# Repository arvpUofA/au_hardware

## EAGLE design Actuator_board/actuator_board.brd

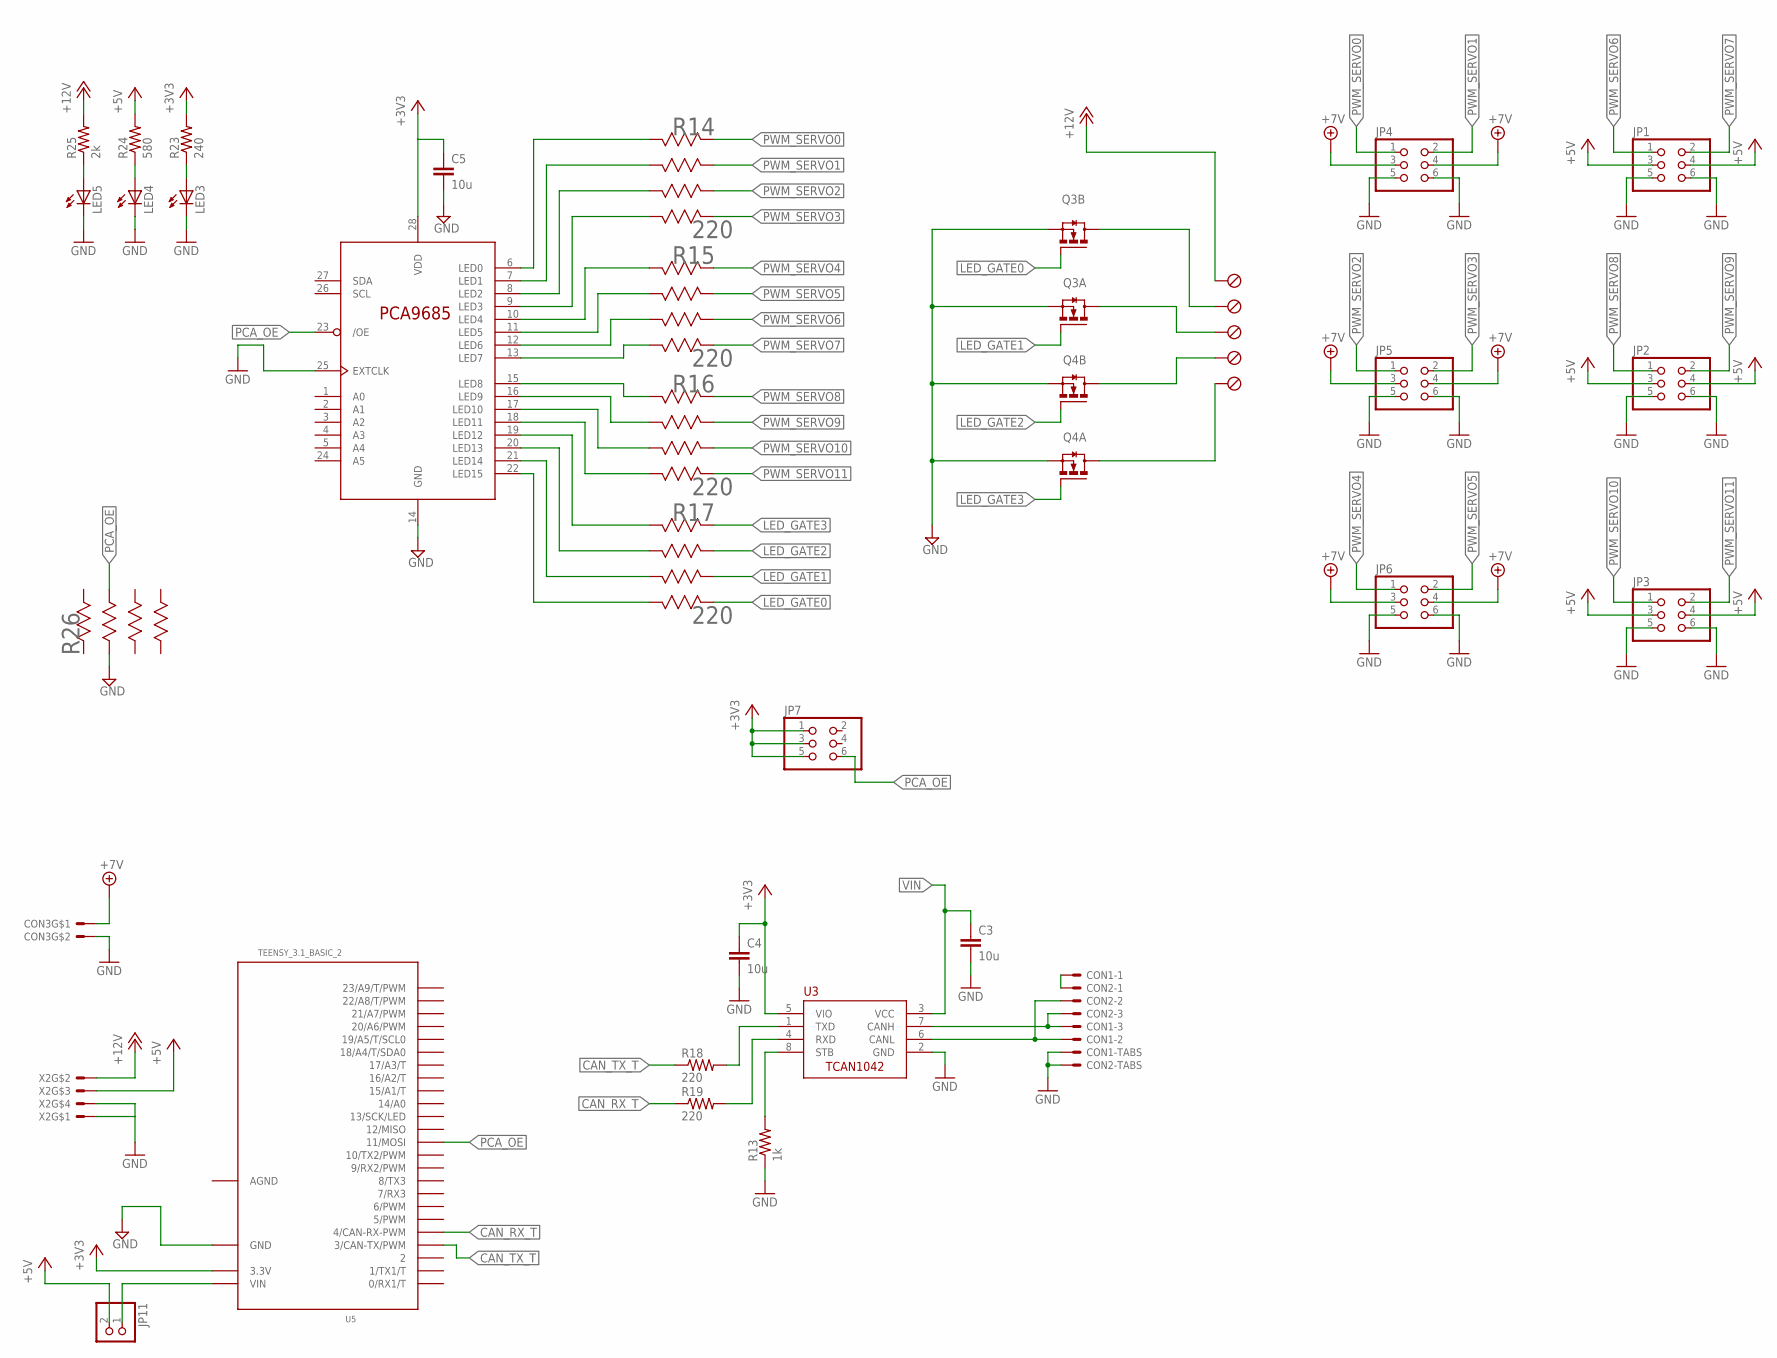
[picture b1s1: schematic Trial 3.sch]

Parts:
C3, C4, C5: 10u; C0805
CON1, CON2: SM03B-GHS-TB
CON3: MOLEX_5566-2; 5566-2
JP1, JP2, JP3, JP4, JP5, JP6, JP7: PINHD-2X3; 2X03
JP11: PINHD-1X2; 1X02
LED3, LED4, LED5: LEDCHIPLED_1206; CHIPLED_1206
Q3, Q4: IRL6372TRPBF; SO-8
R13: 1k; R0805
R14, R15, R16, R17: 220; EXBV8V-M
R18, R19: 220; R0805
R23: 240; R1206
R24: 580; R1206
R25: 2k; R1206
R26: 10k; EXBV8V-M
U3: TCAN1042HVDR; SO-8
U4: PCA9685PW; TSSOP28
U5: TEENSY_3.1_BASIC_2
U$1: SCREWLESS_TERMINAL_HEADERSCREWLESS_TERMINAL_HEADER; 1989777_TERMINALHEADER
X2: MOLEX_5566-4; 5566-4

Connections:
+3V3: C4.1, C5.1, JP7.1, JP7.3, JP7.5, R23.2, U3.5 (VIO), U4.28 (VDD), U5.3.3V
+5V: JP1.3, JP1.4, JP2.3, JP2.4, JP3.3, JP3.4, JP11.2, R24.2, X2.3
+7V: CON3.1, JP4.3, JP4.4, JP5.3, JP5.4, JP6.3, JP6.4
+12V: R25.2, U$1.P$5 (12+), X2.2; also elsewhere on the board
AGND: U5.AGND
CANH: CON1.P$3, CON2.P$3, U3.7 (CANH)
CANL: CON1.P$2, CON2.P$2, U3.6 (CANL)
CANSH: CON1.P$1, CON2.P$1
CAN_RX: R19.2, U3.4 (RXD)
CAN_RX_T: R19.1, U5.4 (4/CAN-RX-PWM)
CAN_TX1: R18.2, U3.1 (TXD)
CAN_TX_T: R18.1, U5.3 (3/CAN-TX/PWM)
GND: C3.2, C4.2, C5.2, CON1.P$4, CON1.P$5, CON2.P$4, CON2.P$5, CON3.2, JP1.5, JP1.6, JP2.5, JP2.6, JP3.5, JP3.6, JP4.5, JP4.6, JP5.5, JP5.6, JP6.5, JP6.6, LED3.C, LED4.C, LED5.C, Q3.1 (S), Q3.3 (S), Q4.1 (S), Q4.3 (S), R13.1, R26.2 (23), U3.2 (GND), U4.14 (GND), U4.25 (EXTCLK), U5.GND, X2.1, X2.4
LED_DRAIN0: Q3.7 (D), Q3.8 (D), U$1.P$4 (LED0); also elsewhere on the board
LED_DRAIN1: Q3.5 (D), Q3.6 (D), U$1.P$3 (LED1); also elsewhere on the board
LED_DRAIN2: Q4.7 (D), Q4.8 (D), U$1.P$2 (LED2); also elsewhere on the board
LED_DRAIN3: Q4.5 (D), Q4.6 (D), U$1.P$1 (LED3); also elsewhere on the board
LED_GATE0: Q3.2 (G), R17.4 (47)
LED_GATE1: Q3.4 (G), R17.3 (35)
LED_GATE2: Q4.2 (G), R17.2 (23)
LED_GATE3: Q4.4 (G), R17.1 (11)
unnamed: LED3.A, R23.1
unnamed: LED4.A, R24.1
unnamed: LED5.A, R25.1
PCA_OE: JP7.6, R26.7 (74), U4.23 (/OE), U5.11 (11/MOSI)
PWM_CH0: R14.8 (82), U4.6 (LED0)
PWM_CH1: R14.7 (74), U4.7 (LED1)
PWM_CH2: R14.6 (66), U4.8 (LED2)
PWM_CH3: R14.5 (58), U4.9 (LED3)
PWM_CH4: R15.8 (82), U4.10 (LED4)
PWM_CH5: R15.7 (74), U4.11 (LED5)
PWM_CH6: R15.6 (66), U4.12 (LED6)
PWM_CH7: R15.5 (58), U4.13 (LED7)
PWM_CH8: R16.8 (82), U4.15 (LED8)
PWM_CH9: R16.7 (74), U4.16 (LED9)
PWM_CH10: R16.6 (66), U4.17 (LED10)
PWM_CH11: R16.5 (58), U4.18 (LED11)
PWM_CH12: R17.8 (82), U4.19 (LED12)
PWM_CH13: R17.7 (74), U4.20 (LED13)
PWM_CH14: R17.6 (66), U4.21 (LED14)
PWM_CH15: R17.5 (58), U4.22 (LED15)
PWM_SERVO0: JP4.1, R14.1 (11)
PWM_SERVO1: JP4.2, R14.2 (23)
PWM_SERVO2: JP5.1, R14.3 (35)
PWM_SERVO3: JP5.2, R14.4 (47)
PWM_SERVO4: JP6.1, R15.1 (11)
PWM_SERVO5: JP6.2, R15.2 (23)
PWM_SERVO6: JP1.1, R15.3 (35)
PWM_SERVO7: JP1.2, R15.4 (47)
PWM_SERVO8: JP2.1, R16.1 (11)
PWM_SERVO9: JP2.2, R16.2 (23)
PWM_SERVO10: JP3.1, R16.3 (35)
PWM_SERVO11: JP3.2, R16.4 (47)
STB: R13.2, U3.8 (STB)
VIN: C3.1, JP11.1, U3.3 (VCC), U5.VIN

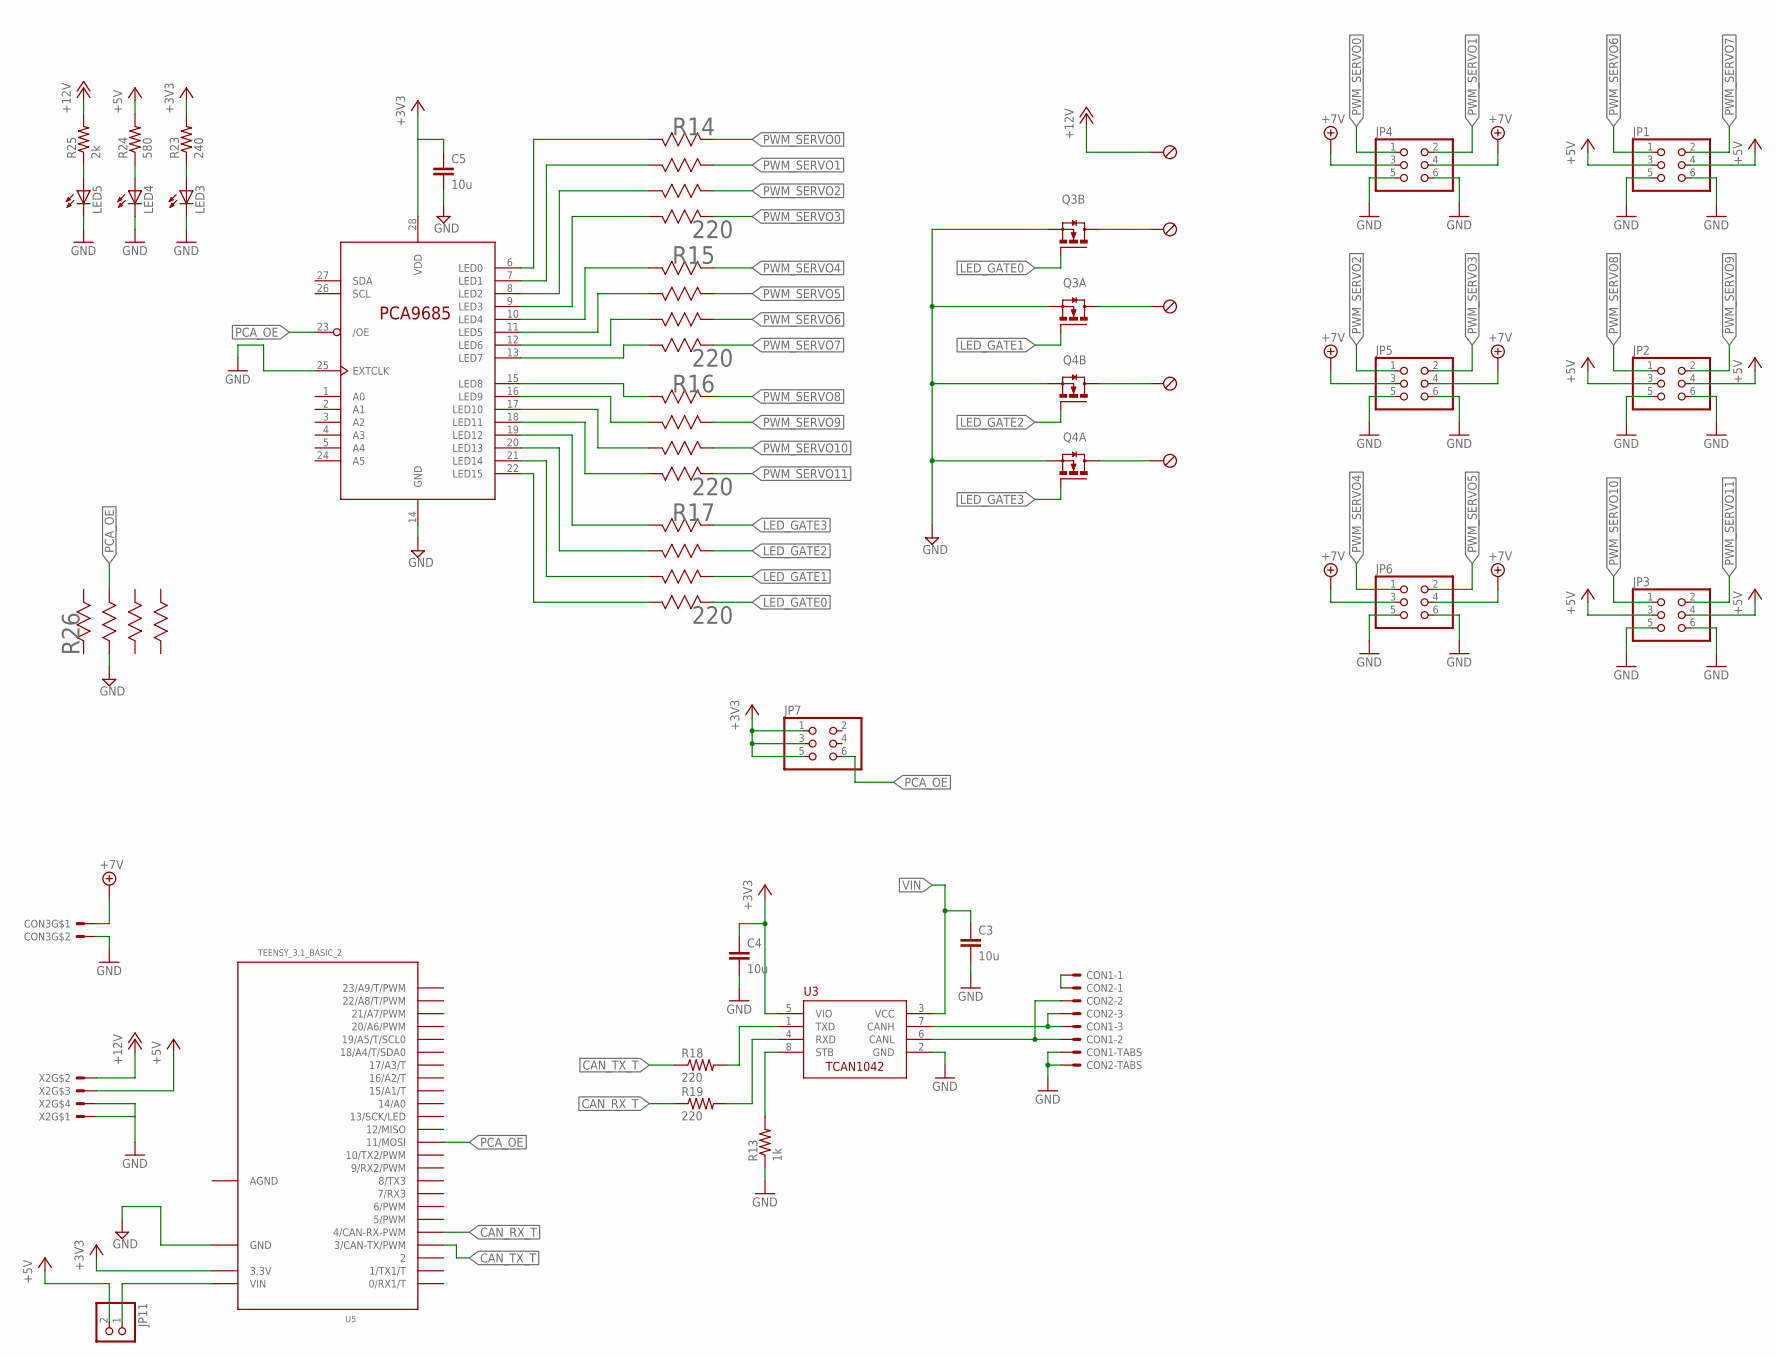
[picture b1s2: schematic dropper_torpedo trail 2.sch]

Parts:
C3, C4, C5: 10u; C0805
CON1, CON2: SM03B-GHS-TB
CON3: MOLEX_5566-2; 5566-2
JP1, JP2, JP3, JP4, JP5, JP6, JP7: PINHD-2X3; 2X03
JP11: PINHD-1X2; 1X02
LED3, LED4, LED5: LEDCHIPLED_1206; CHIPLED_1206
Q3, Q4: IRL6372TRPBF; SO-8
R13: 1k; R0805
R14, R15, R16, R17: 220; EXBV8V-M
R18, R19: 220; R0805
R23: 240; R1206
R24: 580; R1206
R25: 2k; R1206
R26: 10k; EXBV8V-M
U3: TCAN1042HVDR; SO-8
U4: PCA9685PW; TSSOP28
U5: TEENSY_3.1_BASIC_2
X1: OSTVN05A150
X2: MOLEX_5566-4; 5566-4

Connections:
+3V3: C4.1, C5.1, JP7.1, JP7.3, JP7.5, R23.2, U3.5 (VIO), U4.28 (VDD), U5.3.3V
+5V: JP1.3, JP1.4, JP2.3, JP2.4, JP3.3, JP3.4, JP11.2, R24.2, X2.3
+7V: CON3.1, JP4.3, JP4.4, JP5.3, JP5.4, JP6.3, JP6.4
+12V: R25.2, X1.P$5, X2.2; also elsewhere on the board
AGND: U5.AGND
CANH: CON1.P$3, CON2.P$3, U3.7 (CANH)
CANL: CON1.P$2, CON2.P$2, U3.6 (CANL)
CANSH: CON1.P$1, CON2.P$1
CAN_RX: R19.2, U3.4 (RXD)
CAN_RX_T: R19.1, U5.4 (4/CAN-RX-PWM)
CAN_TX1: R18.2, U3.1 (TXD)
CAN_TX_T: R18.1, U5.3 (3/CAN-TX/PWM)
GND: C3.2, C4.2, C5.2, CON1.P$4, CON1.P$5, CON2.P$4, CON2.P$5, CON3.2, JP1.5, JP1.6, JP2.5, JP2.6, JP3.5, JP3.6, JP4.5, JP4.6, JP5.5, JP5.6, JP6.5, JP6.6, LED3.C, LED4.C, LED5.C, Q3.1 (S), Q3.3 (S), Q4.1 (S), Q4.3 (S), R13.1, R26.2 (23), U3.2 (GND), U4.14 (GND), U4.25 (EXTCLK), U5.GND, X2.1, X2.4
LED_DRAIN0: Q3.7 (D), Q3.8 (D), X1.P$4; also elsewhere on the board
LED_DRAIN1: Q3.5 (D), Q3.6 (D), X1.P$3; also elsewhere on the board
LED_DRAIN2: Q4.7 (D), Q4.8 (D), X1.P$2; also elsewhere on the board
LED_DRAIN3: Q4.5 (D), Q4.6 (D), X1.P$1; also elsewhere on the board
LED_GATE0: Q3.2 (G), R17.4 (47)
LED_GATE1: Q3.4 (G), R17.3 (35)
LED_GATE2: Q4.2 (G), R17.2 (23)
LED_GATE3: Q4.4 (G), R17.1 (11)
unnamed: LED3.A, R23.1
unnamed: LED4.A, R24.1
unnamed: LED5.A, R25.1
PCA_OE: JP7.6, R26.7 (74), U4.23 (/OE), U5.11 (11/MOSI)
PWM_CH0: R14.8 (82), U4.6 (LED0)
PWM_CH1: R14.7 (74), U4.7 (LED1)
PWM_CH2: R14.6 (66), U4.8 (LED2)
PWM_CH3: R14.5 (58), U4.9 (LED3)
PWM_CH4: R15.8 (82), U4.10 (LED4)
PWM_CH5: R15.7 (74), U4.11 (LED5)
PWM_CH6: R15.6 (66), U4.12 (LED6)
PWM_CH7: R15.5 (58), U4.13 (LED7)
PWM_CH8: R16.8 (82), U4.15 (LED8)
PWM_CH9: R16.7 (74), U4.16 (LED9)
PWM_CH10: R16.6 (66), U4.17 (LED10)
PWM_CH11: R16.5 (58), U4.18 (LED11)
PWM_CH12: R17.8 (82), U4.19 (LED12)
PWM_CH13: R17.7 (74), U4.20 (LED13)
PWM_CH14: R17.6 (66), U4.21 (LED14)
PWM_CH15: R17.5 (58), U4.22 (LED15)
PWM_SERVO0: JP4.1, R14.1 (11)
PWM_SERVO1: JP4.2, R14.2 (23)
PWM_SERVO2: JP5.1, R14.3 (35)
PWM_SERVO3: JP5.2, R14.4 (47)
PWM_SERVO4: JP6.1, R15.1 (11)
PWM_SERVO5: JP6.2, R15.2 (23)
PWM_SERVO6: JP1.1, R15.3 (35)
PWM_SERVO7: JP1.2, R15.4 (47)
PWM_SERVO8: JP2.1, R16.1 (11)
PWM_SERVO9: JP2.2, R16.2 (23)
PWM_SERVO10: JP3.1, R16.3 (35)
PWM_SERVO11: JP3.2, R16.4 (47)
STB: R13.2, U3.8 (STB)
VIN: C3.1, JP11.1, U3.3 (VCC), U5.VIN

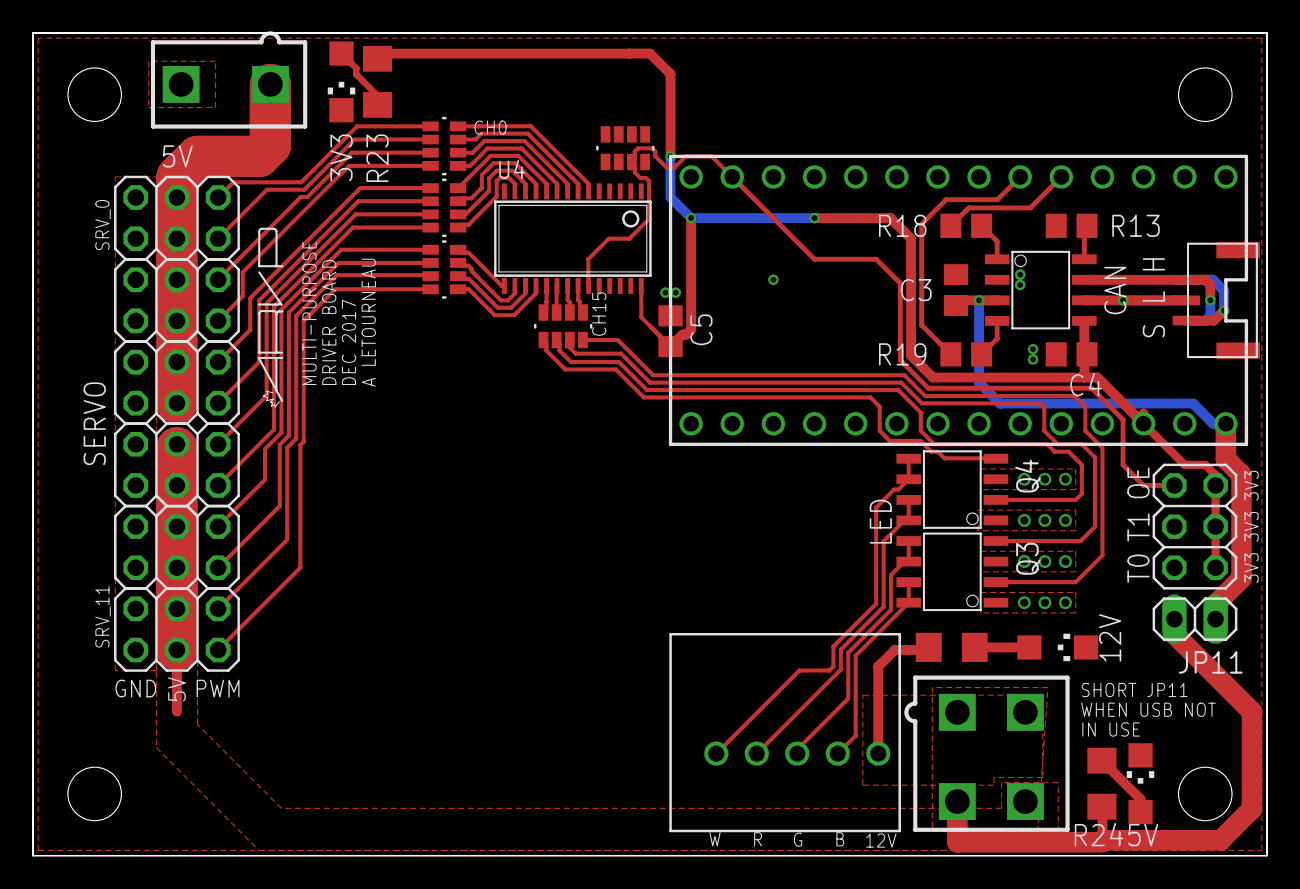
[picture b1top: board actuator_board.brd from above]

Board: 2 copper layers, 76.2 x 50.8 mm, 42 parts (1 on the bottom side), 54 nets.

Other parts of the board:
U$5: LOGO3
U$6: LETTER_L
U$7: DOCFIELD
U$8, U$9, U$10, U$11: STAND-OFF

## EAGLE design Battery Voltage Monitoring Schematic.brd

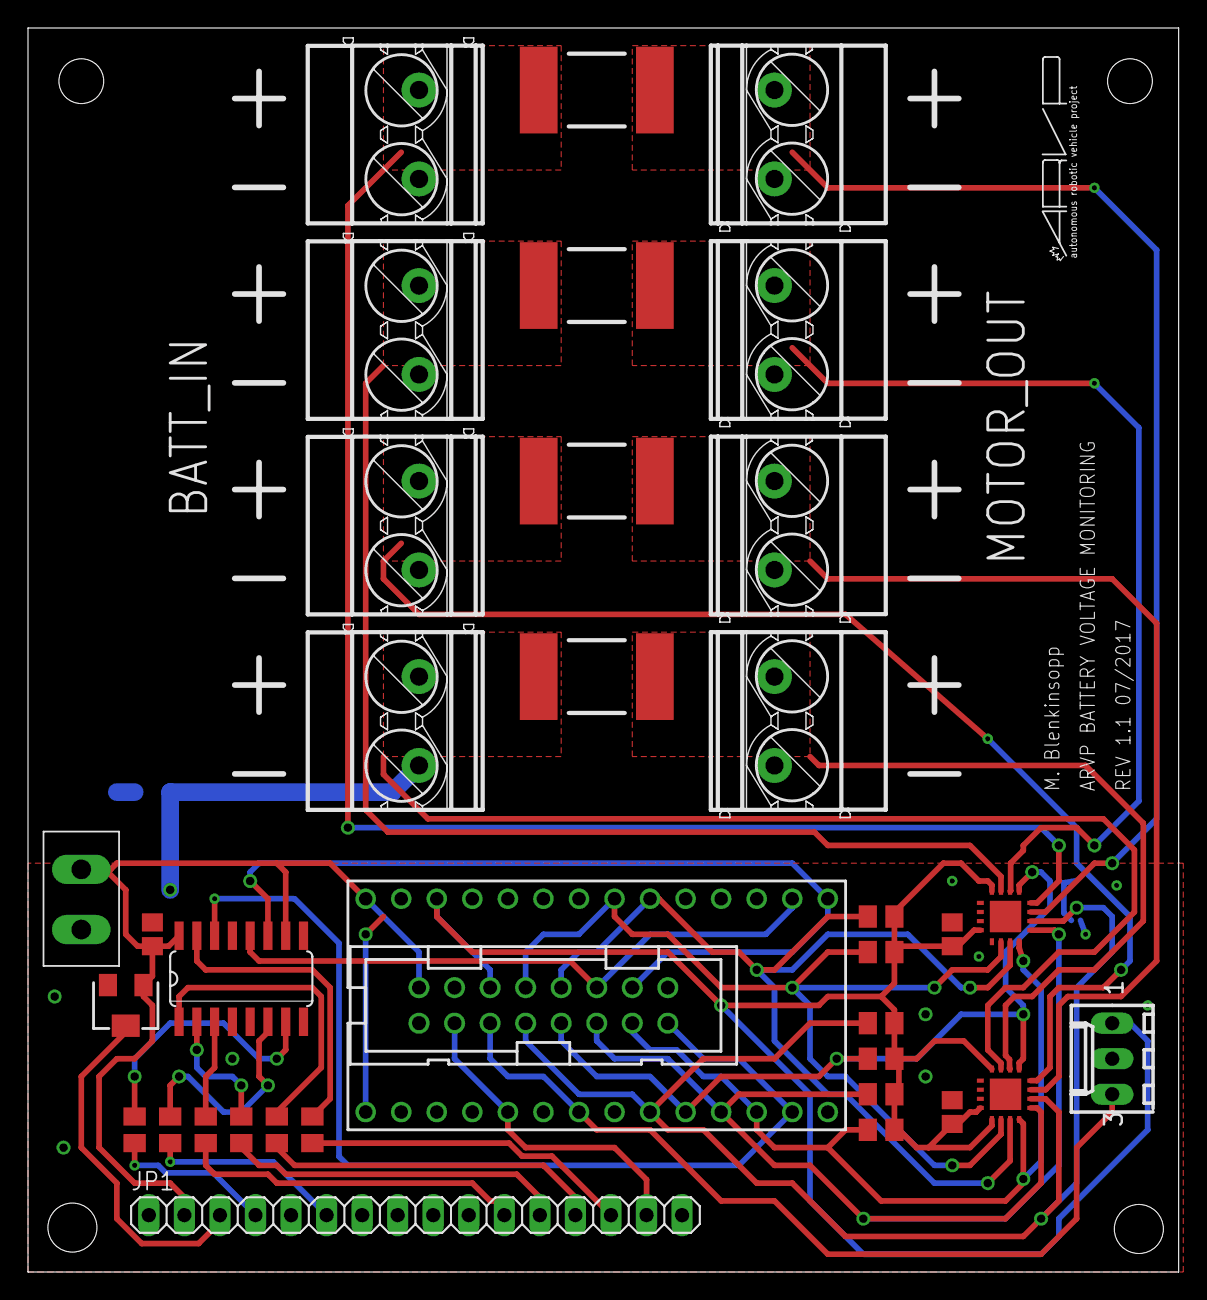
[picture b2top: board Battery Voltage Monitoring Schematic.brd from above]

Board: 2 copper layers, 82.2 x 88.9 mm, 37 parts (0 on the bottom side), 36 nets.

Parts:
C1, C2, C4: 0.1microF; C2012
IC1: 74HC595D; SO16
J1: 22-27-2031-03; 6410-03
JP1: 1X16
R1, R3, R4, R7: 0.001Ohm; 3920
R2, R5, R6, R8, R9, R10: 10kOhm; M2012
R11, R12, R13, R14, R15, R16: 560Ohm; M2012
R22: 10kOhm; SM-42/43W
U1, U2: INA3221.; HVQFN16_4X4
U$1, U$2, U$3, U$4, U$5, U$6, U$7, U$11: MKDS_5/2-6,352; MKDS_5/2-6,35
U$9: ARVP_MOLEX_FEMALE
U$10: ARVP_LOGO; ARVP
U$14: TEENSY_3.1-3.2_DIL; TEENSY_3.0-3.2&LC_DIL
X3: 2516-; PAK100/2500-16

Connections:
0-26V_BATTERY1: R4.P$2, U1.12, U$1.1
0-26V_BATTERY2: R1.P$2, U1.15, U$2.1
0-26V_BATTERY3: R3.P$2, U2.12, U$3.1
0-26V_BATTERY4: R7.P$2, U2.15, U$4.1
3.3V: C2.1, C4.1, J1.1, R2.1, R5.2, R6.2, R8.2, R9.2, R10.2, U1.4, U1.16, U2.4, U2.5, U2.16, U$14.3.3V, X3.6
+5V: C1.1, IC1.10, IC1.16, JP1.2, R22.1, U$9.P$1, U$14.VIN, X3.2
AGND: U$14.AGND, X3.4
BACKLIGHT: JP1.15, U$14.3, X3.3
CRITICAL_OUT: R8.1, U1.9, U2.9, U$14.9, X3.11
DATA: IC1.14, U$14.11, X3.15
ENABLE: JP1.6, R12.2
ENABLE1: IC1.6, R12.1
GND: C1.2, C2.2, C4.2, IC1.5, IC1.8, IC1.13, J1.2, JP1.1, JP1.5, JP1.16, R22.3, U1.3, U1.5, U2.3, U$1.2, U$2.2, U$3.2, U$4.2, U$5.1, U$6.1, U$7.1, U$9.P$2, U$11.1, U$14.GND, X3.1
HALL: J1.3, U$14.5, X3.5
LATCH: IC1.12, U$14.14/A0, X3.12
LCD(SCK): IC1.11, U$14.13, X3.14
LCD_DB4: JP1.11, R13.2
LCD_DB5: JP1.12, R14.2
LCD_DB6: JP1.13, R15.2
LCD_DB7: JP1.14, R16.1
LCD_DB41: IC1.3, R13.1
LCD_DB51: IC1.2, R14.1
LCD_DB61: IC1.1, R15.1
LCD_DB71: IC1.15, R16.2
MOTOR1: R4.P$1, U1.11, U$7.2
MOTOR2: R1.P$1, U1.14, U$6.2
MOTOR3: R3.P$1, U2.11, U$5.2
MOTOR4: R7.P$1, U2.14, U$11.2
unnamed: JP1.3, R22.2
PV_OUT: R2.2, U1.10, U2.10, U$14.7, X3.7
RS: JP1.4, R11.2
RS1: IC1.7, R11.1
SDA_OUT: R6.1, U1.7, U2.7, U$14.18/A4, X3.10
TC_OUT: R9.1, U1.13, U2.13, U$14.8, X3.9
TEENSY_SCK: R5.1, U1.6, U2.6, U$14.19/A5, X3.8
WARNING_OUT: R10.1, U1.8, U2.8, U$14.10, X3.13

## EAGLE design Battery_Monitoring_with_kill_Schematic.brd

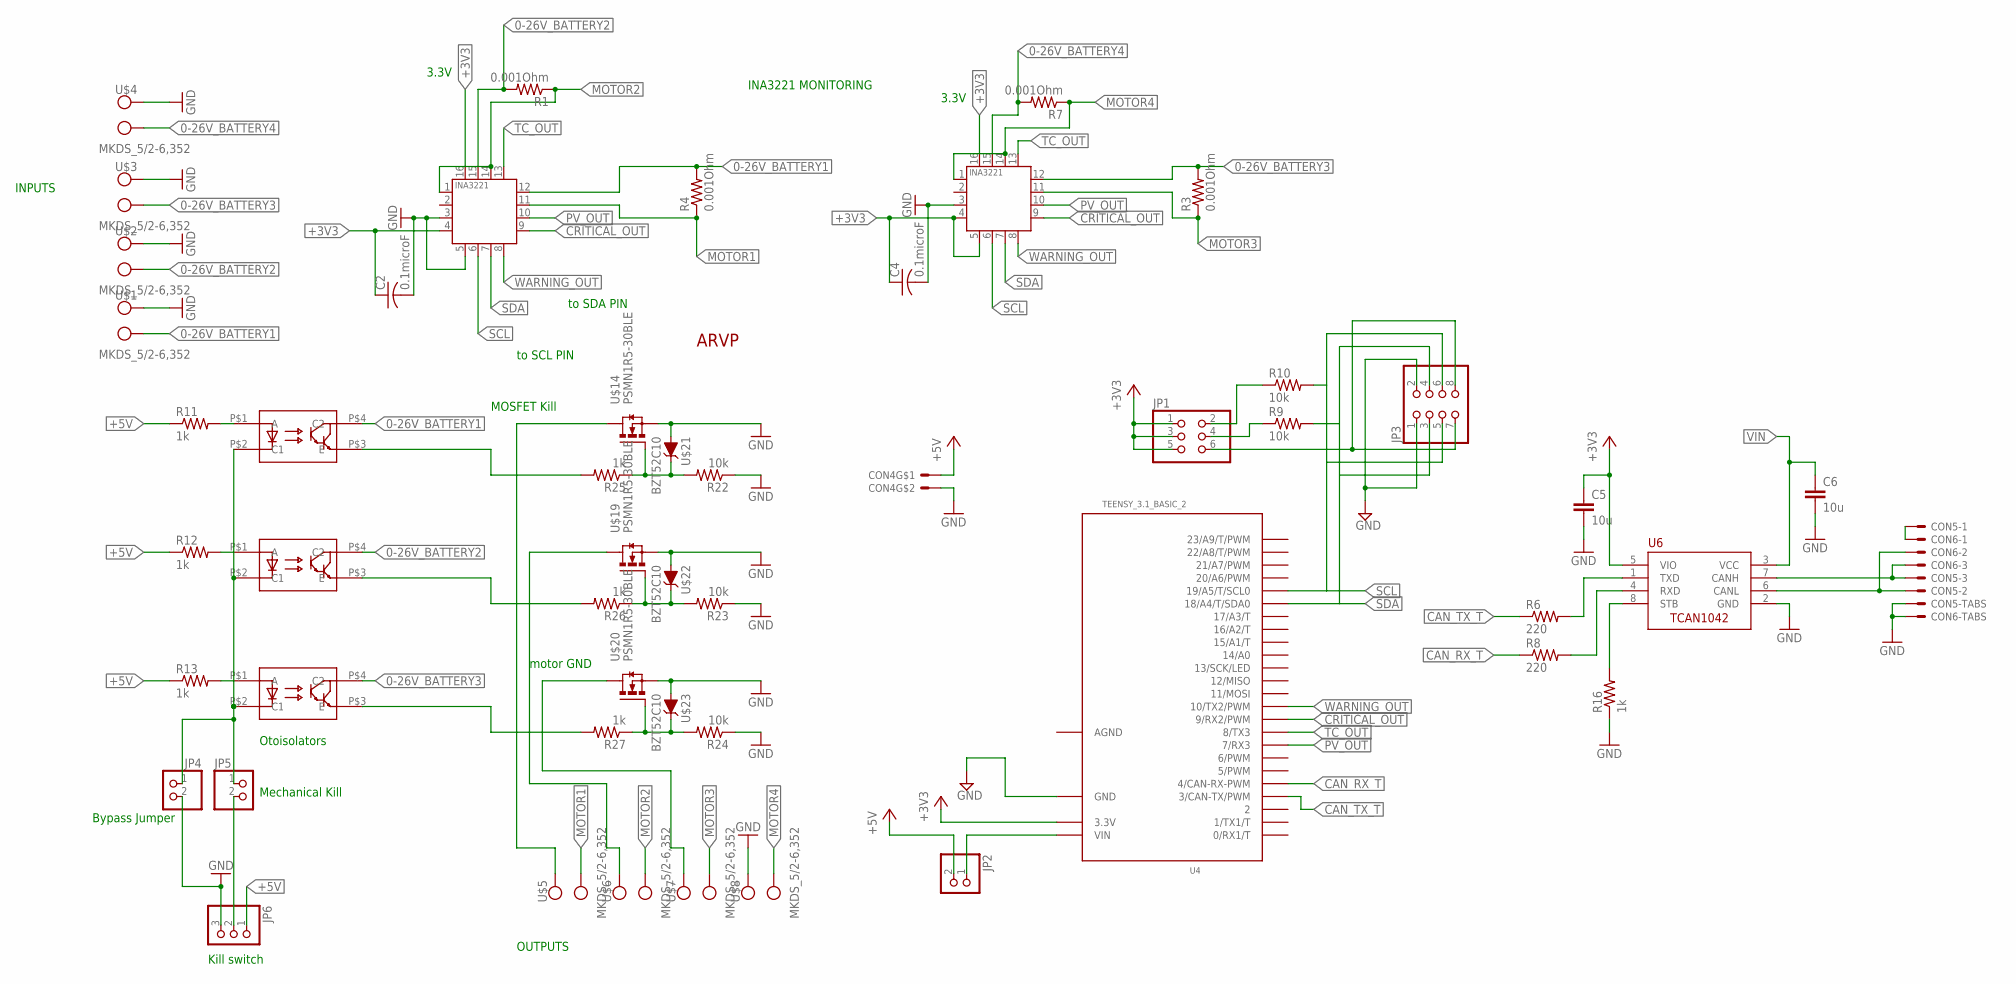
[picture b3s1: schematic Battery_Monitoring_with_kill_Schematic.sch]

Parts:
C2, C4: 0.1microF; C2012
C5, C6: 10u; C0805
CON4: MOLEX_5566-2; 5566-2
CON5, CON6: S3B-PH-SM4-TB
JP1: PINHD-2X3; 2X03
JP2, JP4, JP5: PINHD-1X2; 1X02
JP3: PINHD-2X4; 2X04
JP6: PINHD-1X3; 1X03
R1, R3, R4, R7: 0.001Ohm; 3920
R6, R8: 220; R0805
R9, R10: 10k; R1206
R11, R12, R13, R16: 1k; R0805
R22, R23, R24: 10k; M1206
R25, R26, R27: 1k; M1206
U1, U2: INA3221.; HVQFN16_4X4
U4: TEENSY_3.1_BASIC_2
U6: TCAN1042HVDR; SO-8
U$1, U$2, U$3, U$4, U$5, U$6, U$7, U$8: MKDS_5/2-6,352; MKDS_5/2-6,35
U$10: ARVP_LOGO; ARVP
U$11, U$12, U$13: TCLD1000CT; SOP-4L
U$14, U$19, U$20: PSMN1R5-30BLE; SOT404/D2PAK
U$21, U$22, U$23: BZT52C10; SOD-123

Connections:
0-26V_BATTERY1: R4.P$2 (2), U1.12 (IN+1), U$1.1 (KL), U$11.P$4 (C2)
0-26V_BATTERY2: R1.P$2 (2), U1.15 (IN+2), U$2.1 (KL), U$12.P$4 (C2)
0-26V_BATTERY3: R3.P$2 (2), U2.12 (IN+1), U$3.1 (KL), U$13.P$4 (C2)
0-26V_BATTERY4: R7.P$2 (2), U2.15 (IN+2), U$4.1 (KL)
+3V3: C2.1, C4.1, C5.1, JP1.1, JP1.3, JP1.5, U1.4 (VS), U1.16 (VPU), U2.4 (VS), U2.5 (A0), U2.16 (VPU), U4.3.3V, U6.5 (VIO)
+5V: CON4.1, JP2.2, JP6.1, R11.1, R12.1, R13.1
AGND: U4.AGND
CANH1: CON5.P$3, CON6.P$3, U6.7 (CANH)
CANL1: CON5.P$2, CON6.P$2, U6.6 (CANL)
CANSH1: CON5.P$1, CON6.P$1
CAN_RX1: R8.2, U6.4 (RXD)
CAN_RX_T: R8.1, U4.4 (4/CAN-RX-PWM)
CAN_TX2: R6.2, U6.1 (TXD)
CAN_TX_T: R6.1, U4.3 (3/CAN-TX/PWM)
CRITICAL_OUT: U1.9 (CRITICAL), U2.9 (CRITICAL), U4.9 (9/RX2/PWM)
E1: R25.2, U$11.P$3 (E)
E2: R26.2, U$12.P$3 (E)
E3: R27.2, U$13.P$3 (E)
GND: C2.2, C4.2, C5.2, C6.2, CON4.2, CON5.P$4, CON5.P$5, CON6.P$4, CON6.P$5, JP3.1, JP3.2, JP4.2, JP6.3, R16.1, R22.1, R23.1, R24.1, U1.3 (GND), U1.5 (A0), U2.3 (GND), U4.GND, U6.2 (GND), U$1.2 (KL1), U$2.2 (KL1), U$3.2 (KL1), U$4.2 (KL1), U$8.2 (KL1), U$14.3S (S), U$19.3S (S), U$20.3S (S), U$21.P$2 (A), U$22.P$2 (A), U$23.P$2 (A)
I2C_3V1: JP1.6, JP3.7, JP3.8
MD1: U$5.2 (KL1), U$14.2D (D)
MD2: U$6.2 (KL1), U$19.2D (D)
MD3: U$7.2 (KL1), U$20.2D (D)
MG1: R22.2, R25.1, U$14.1G (G), U$21.P$1 (C)
MG2: R23.2, R26.1, U$19.1G (G), U$22.P$1 (C)
MG3: R24.2, R27.1, U$20.1G (G), U$23.P$1 (C)
MOTOR1: R4.P$1 (1), U1.11 (IN-1), U$5.1 (KL)
MOTOR2: R1.P$1 (1), U1.1 (IN-3), U1.14 (IN-2), U$6.1 (KL)
MOTOR3: R3.P$1 (1), U2.11 (IN-1), U$7.1 (KL)
MOTOR4: R7.P$1 (1), U2.1 (IN-3), U2.14 (IN-2), U$8.1 (KL)
unnamed: R11.2, U$11.P$1 (A)
unnamed: R12.2, U$12.P$1 (A)
unnamed: R13.2, U$13.P$1 (A)
unnamed: JP4.1, JP5.1, U$11.P$2 (C1), U$12.P$2 (C1), U$13.P$2 (C1)
unnamed: JP5.2, JP6.2
PV_OUT: U1.10 (PV), U2.10 (PV), U4.7 (7/RX3)
SCL: JP3.5, JP3.6, R10.2, U1.6 (SCL), U2.6 (SCL), U4.19/A5 (19/A5/T/SCL0)
SCL_3V1: JP1.2, R10.1
SDA: JP3.3, JP3.4, R9.2, U1.7 (SDA), U2.7 (SDA), U4.18/A4 (18/A4/T/SDA0)
SDA_3V1: JP1.4, R9.1
STB1: R16.2, U6.8 (STB)
TC_OUT: U1.13 (TC), U2.13 (TC), U4.8 (8/TX3)
VIN: C6.1, JP2.1, U4.VIN, U6.3 (VCC)
WARNING_OUT: U1.8 (WARNING), U2.8 (WARNING), U4.10 (10/TX2/PWM)

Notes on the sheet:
3.3V
Kill switch
motor GND
INPUTS
INA3221 MONITORING
Otoisolators
OUTPUTS
MOSFET Kill
to SDA PIN
to SCL PIN
Mechanical Kill
Bypass Jumper

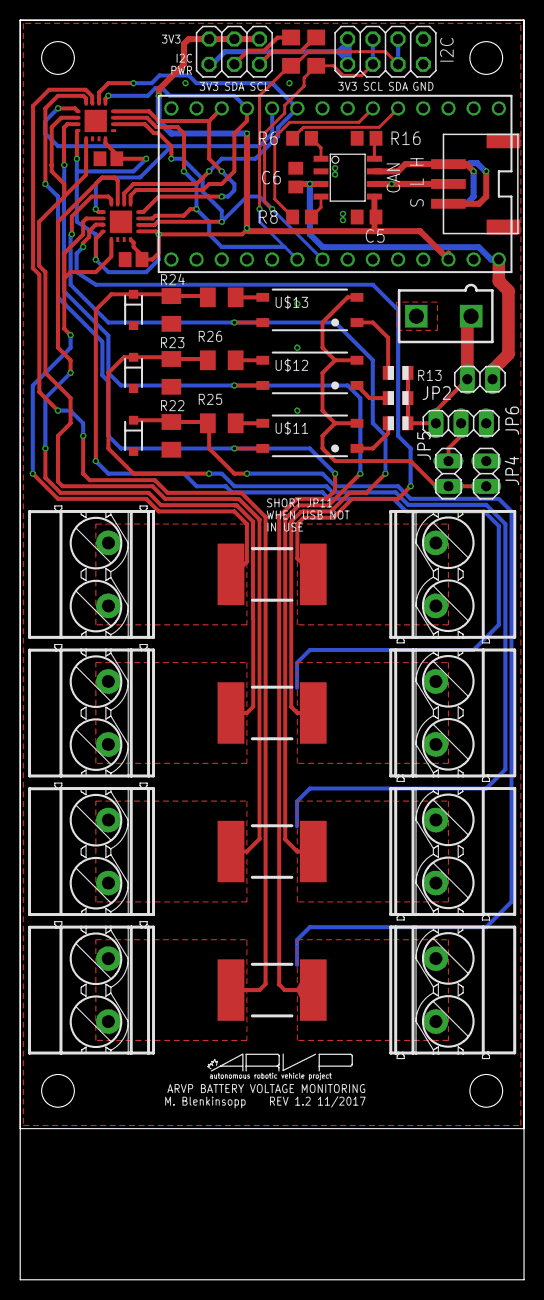
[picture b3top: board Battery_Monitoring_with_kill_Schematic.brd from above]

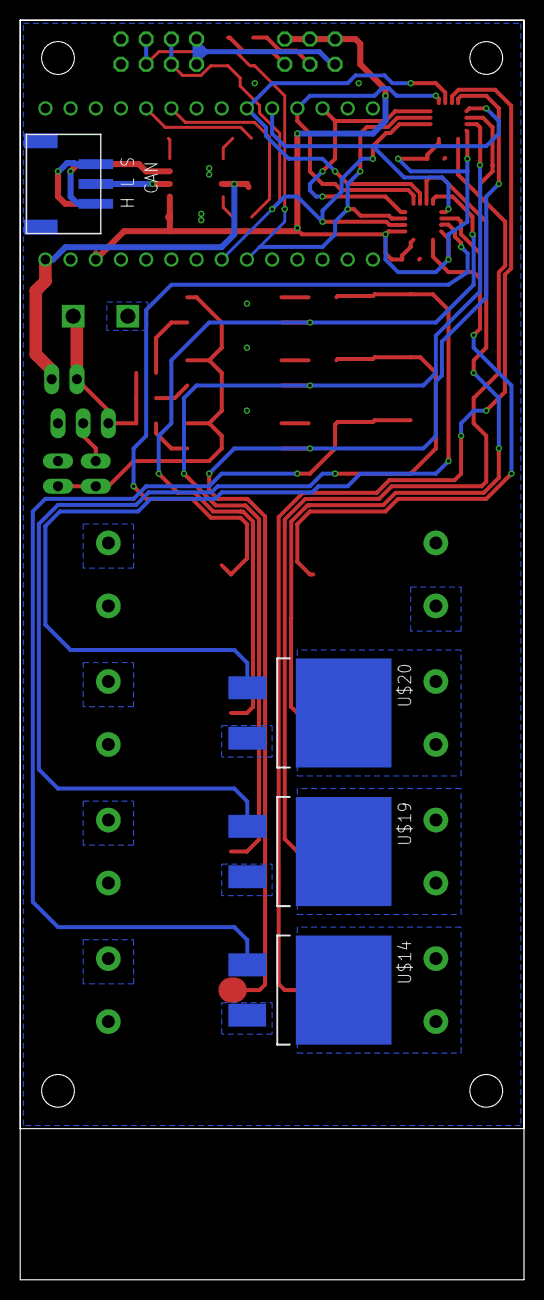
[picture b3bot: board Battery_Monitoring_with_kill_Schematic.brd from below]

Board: 2 copper layers, 50.8 x 127.0 mm, 57 parts (4 on the bottom side), 43 nets.

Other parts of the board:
U$18, U$24, U$25, U$26: STAND-OFF

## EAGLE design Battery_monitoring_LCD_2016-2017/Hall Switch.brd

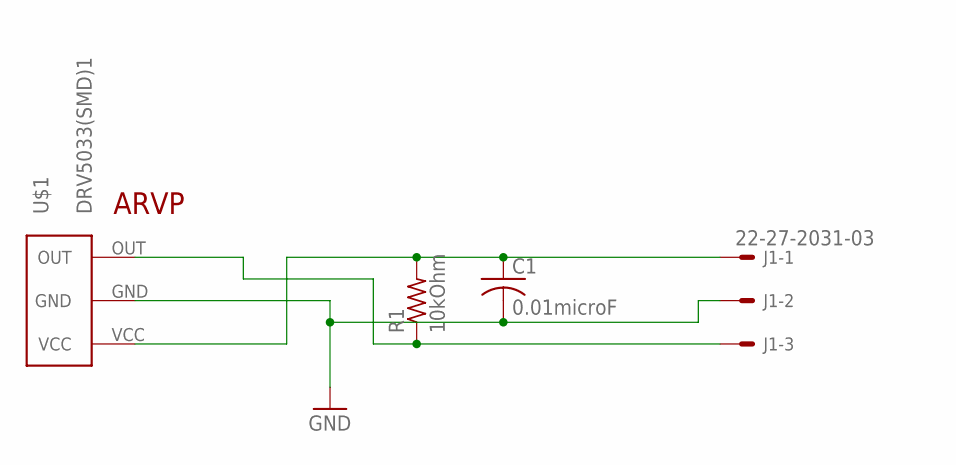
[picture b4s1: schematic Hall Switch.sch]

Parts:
C1: 0.01microF; C2012
J1: 22-27-2031-03; 6410-03
R1: 10kOhm; M2012
U$1: DRV5033(SMD)1; SOT-23
U$2: ARVP_LOGO; ARVP

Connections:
3.3V: C1.1, J1.1, R1.2, U$1.VCC
GND: C1.2, J1.2, U$1.GND
HALL: J1.3, R1.1, U$1.OUT

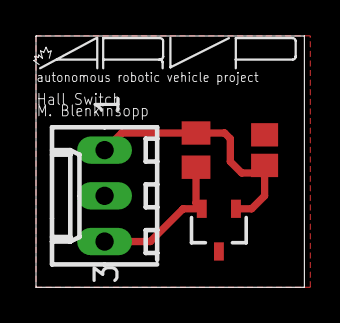
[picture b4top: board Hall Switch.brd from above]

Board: 2 copper layers, 14.9 x 14.0 mm, 5 parts (0 on the bottom side), 3 nets.

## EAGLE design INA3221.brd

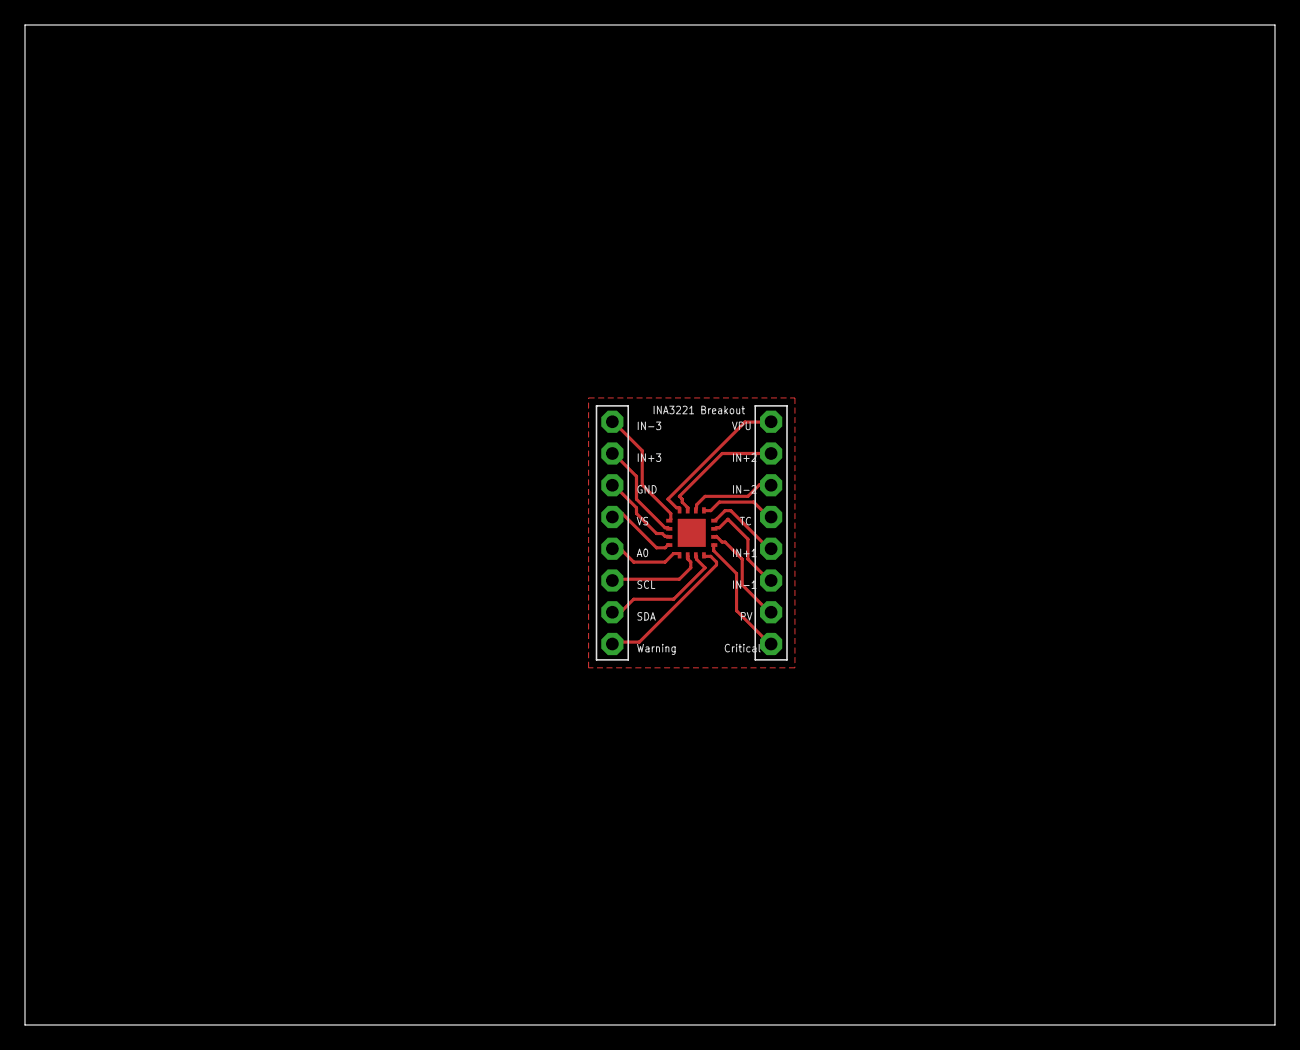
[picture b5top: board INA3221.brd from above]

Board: 2 copper layers, 100.0 x 80.0 mm, 3 parts (0 on the bottom side), 16 nets.

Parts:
JP1, JP2: 1X08-BIG
U1: INA3221.; HVQFN16_4X4

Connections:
unnamed: JP2.8, U1.1
unnamed: JP2.7, U1.2
unnamed: JP2.6, U1.3
unnamed: JP2.5, U1.4
unnamed: JP2.4, U1.5
unnamed: JP2.3, U1.6
unnamed: JP2.2, U1.7
unnamed: JP2.1, U1.8
unnamed: JP1.8, U1.9
unnamed: JP1.7, U1.10
unnamed: JP1.6, U1.11
unnamed: JP1.5, U1.12
unnamed: JP1.4, U1.13
unnamed: JP1.3, U1.14
unnamed: JP1.2, U1.15
unnamed: JP1.1, U1.16
